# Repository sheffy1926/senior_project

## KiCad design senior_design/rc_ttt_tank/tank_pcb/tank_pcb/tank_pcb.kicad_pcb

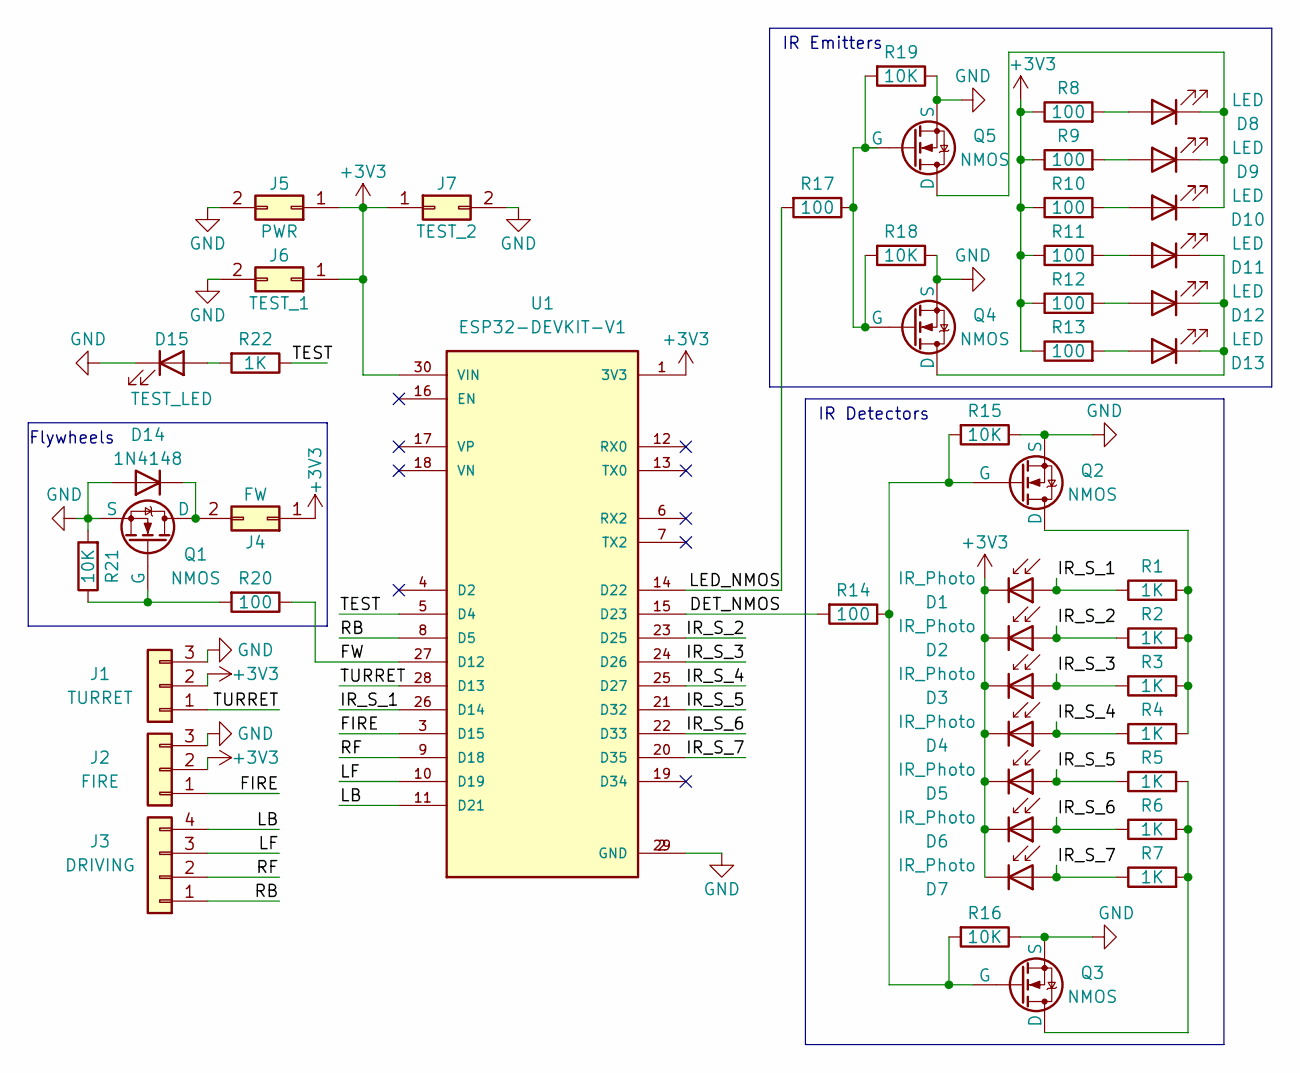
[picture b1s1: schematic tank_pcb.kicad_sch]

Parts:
D1, D2, D3, D4, D5, D6, D7: IR_Photo; LEDRD254W51D580H870
D8, D9, D10, D11, D12, D13: LED; LEDRD254W51D580H870
D14: 1N4148; D_DO-35_SOD27_P7.62mm_Horizontal
D15: TEST_LED; LED_D3.0mm
J1: TURRET; PinHeader_1x03_P2.54mm_Vertical
J2: FIRE; PinHeader_1x03_P2.54mm_Vertical
J3: DRIVING; PinHeader_1x04_P2.54mm_Vertical
J4: FW; PinHeader_1x02_P2.54mm_Vertical
J5: PWR; PinHeader_1x02_P2.54mm_Vertical
J6: TEST_1; PinHeader_1x02_P2.54mm_Vertical
J7: TEST_2; PinHeader_1x02_P2.54mm_Vertical
Q1, Q2, Q3, Q4, Q5: NMOS; SOT95P240X111-3N
R1, R2, R3, R4, R5, R6, R7, R22: 1K; R_Axial_DIN0204_L3.6mm_D1.6mm_P7.62mm_Horizontal
R8, R9, R10, R11, R12, R13, R14, R17, R20: 100; R_Axial_DIN0204_L3.6mm_D1.6mm_P7.62mm_Horizontal
R15, R16, R18, R19, R21: 10K; R_Axial_DIN0204_L3.6mm_D1.6mm_P7.62mm_Horizontal
U1: ESP32-DEVKIT-V1; MODULE_ESP32_DEVKIT_V1; PARTREV N/A

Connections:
+3V3: D1.1 (K), D2.1 (K), D3.1 (K), D4.1 (K), D5.1 (K), D6.1 (K), D7.1 (K), J1.2, J2.2, J4.1, J5.1, J6.1, J7.1, R8.1, R9.1, R10.1, R11.1, R12.1, R13.1, U1.1 (3V3), U1.30 (VIN)
/DET_NMOS: R14.2, U1.15 (D23)
/FIRE: J2.1, U1.3 (D15)
/FW: R20.1, U1.27 (D12)
/IR_S_1: D1.2 (A), R1.1, U1.26 (D14)
/IR_S_2: D2.2 (A), R2.1, U1.23 (D25)
/IR_S_3: D3.2 (A), R3.1, U1.24 (D26)
/IR_S_4: D4.2 (A), R4.1, U1.25 (D27)
/IR_S_5: D5.2 (A), R5.1, U1.21 (D32)
/IR_S_6: D6.2 (A), R6.1, U1.22 (D33)
/IR_S_7: D7.2 (A), R7.1, U1.20 (D35)
/LB: J3.4, U1.11 (D21)
/LED_NMOS: R17.2, U1.14 (D22)
/LF: J3.3, U1.10 (D19)
/RB: J3.1, U1.8 (D5)
/RF: J3.2, U1.9 (D18)
/TEST: R22.1, U1.5 (D4)
/TURRET: J1.1, U1.28 (D13)
GND: D14.2 (A), D15.1 (K), J1.3, J2.3, J5.2, J6.2, J7.2, Q1.3 (S), Q2.3 (S), Q3.3 (S), Q4.3 (S), Q5.3 (S), R15.1, R16.1, R18.1, R19.1, R21.2, U1.2 (GND), U1.29 (GND)
unnamed: D8.2 (A), R8.2
unnamed: D9.2 (A), R9.2
unnamed: D10.2 (A), R10.2
unnamed: D8.1 (K), D9.1 (K), D10.1 (K), Q5.1 (D)
unnamed: D11.2 (A), R11.2
unnamed: D11.1 (K), D12.1 (K), D13.1 (K), Q4.1 (D)
unnamed: D12.2 (A), R12.2
unnamed: D13.2 (A), R13.2
unnamed: D14.1 (K), J4.2, Q1.1 (D)
unnamed: D15.2 (A), R22.2
unnamed: Q1.2 (G), R20.2, R21.1
unnamed: Q2.1 (D), R1.2, R2.2, R3.2, R4.2
unnamed: Q2.2 (G), Q3.2 (G), R14.1, R15.2, R16.2
unnamed: Q3.1 (D), R5.2, R6.2, R7.2
unnamed: Q4.2 (G), Q5.2 (G), R17.1, R18.2, R19.2

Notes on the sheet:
IR Detectors
Flywheels
IR Emitters

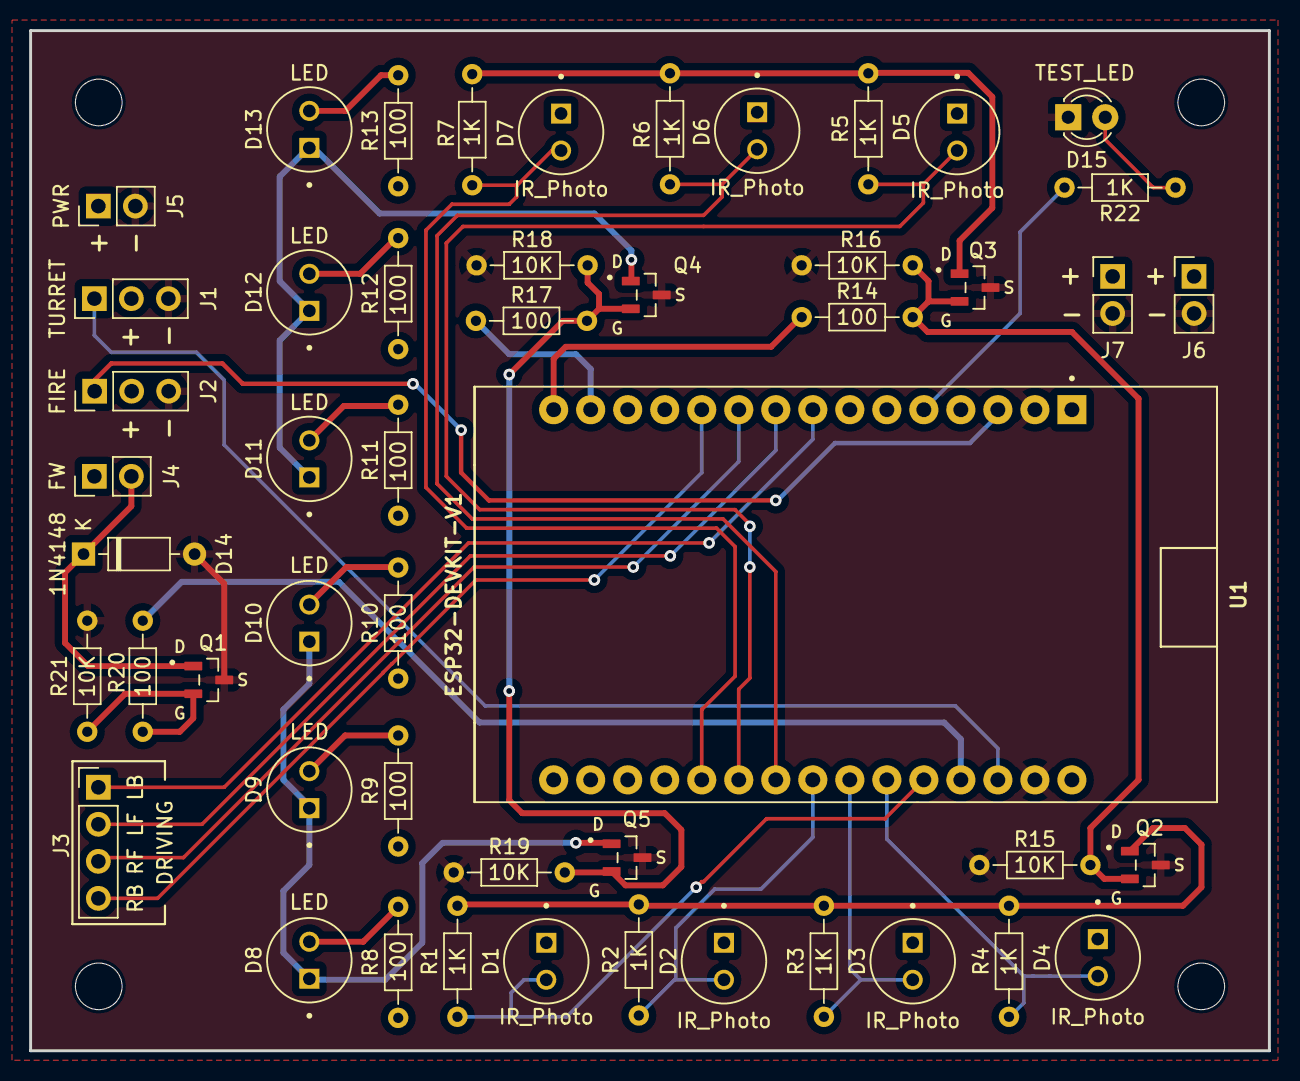
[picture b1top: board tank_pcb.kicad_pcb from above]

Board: 2 copper layers, 85.0 x 70.0 mm, 50 parts (0 on the bottom side), 34 nets.

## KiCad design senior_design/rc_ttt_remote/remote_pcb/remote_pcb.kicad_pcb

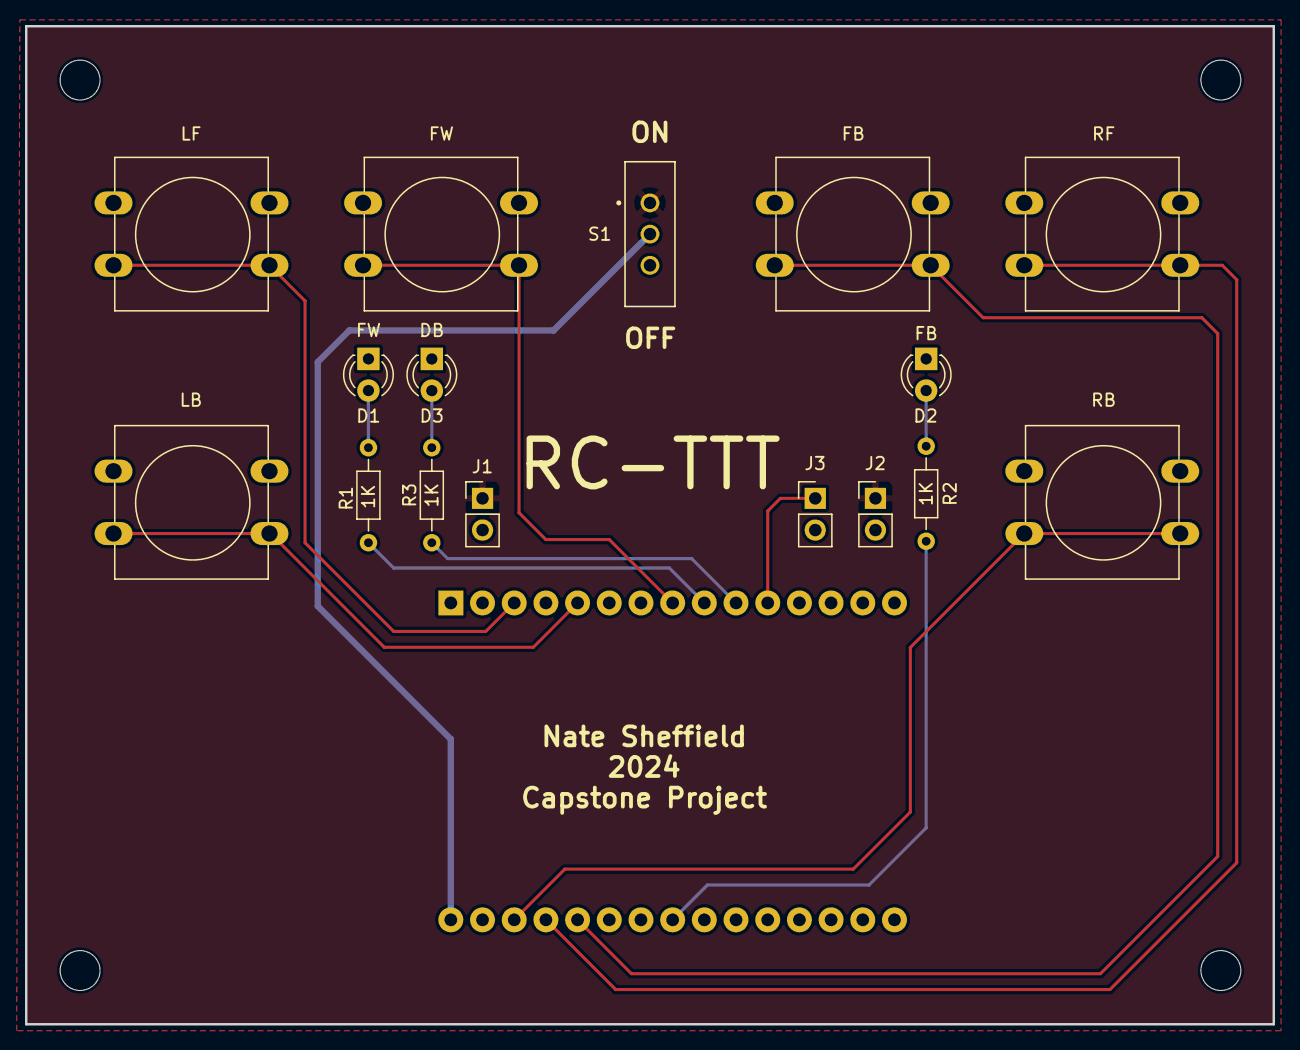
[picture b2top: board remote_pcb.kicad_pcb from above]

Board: 2 copper layers, 100.0 x 80.0 mm, 17 parts (1 on the bottom side), 16 nets.

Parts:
D1: FW; LED_D3.0mm
D2: FB; LED_D3.0mm
D3: DB; LED_D3.0mm
FB: FB; SW_PUSH-12mm
FW: FW; SW_PUSH-12mm
J1: PWR; PinHeader_1x02_P2.54mm_Vertical
J2: PWR_TEST; PinHeader_1x02_P2.54mm_Vertical
J3: PIN_TEST; PinHeader_1x02_P2.54mm_Vertical
LB: LB; SW_PUSH-12mm
LF: LF; SW_PUSH-12mm
R1, R2, R3: 1K; R_Axial_DIN0204_L3.6mm_D1.6mm_P7.62mm_Horizontal
RB: RB; SW_PUSH-12mm
RF: RF; SW_PUSH-12mm
S1: EG1218; SW_EG1218
U2: ESP32-DEVKIT-V1; MODULE_ESP32_DEVKIT_V1

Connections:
+3.3V: J1.1, J2.1, S1.1
GND: D1.1 (K), D2.1 (K), D3.1 (K), FB.1, FW.1, J1.2, J2.2, J3.2, LB.1, LF.1, RB.1, RF.1, U2.2 (GND), U2.29 (GND)
unnamed: D1.2 (A), R1.1
unnamed: D2.2 (A), R2.1
unnamed: D3.2 (A), R3.1
unnamed: J3.1, U2.11 (D21)
unnamed: LB.2, U2.5 (D4)
unnamed: FW.2, U2.8 (D5)
unnamed: RF.2, U2.27 (D12)
unnamed: RB.2, U2.28 (D13)
unnamed: FB.2, U2.26 (D14)
unnamed: LF.2, U2.3 (D15)
unnamed: R1.2, U2.9 (D18)
unnamed: R3.2, U2.10 (D19)
unnamed: R2.2, U2.23 (D25)
unnamed: S1.2, U2.30 (VIN)

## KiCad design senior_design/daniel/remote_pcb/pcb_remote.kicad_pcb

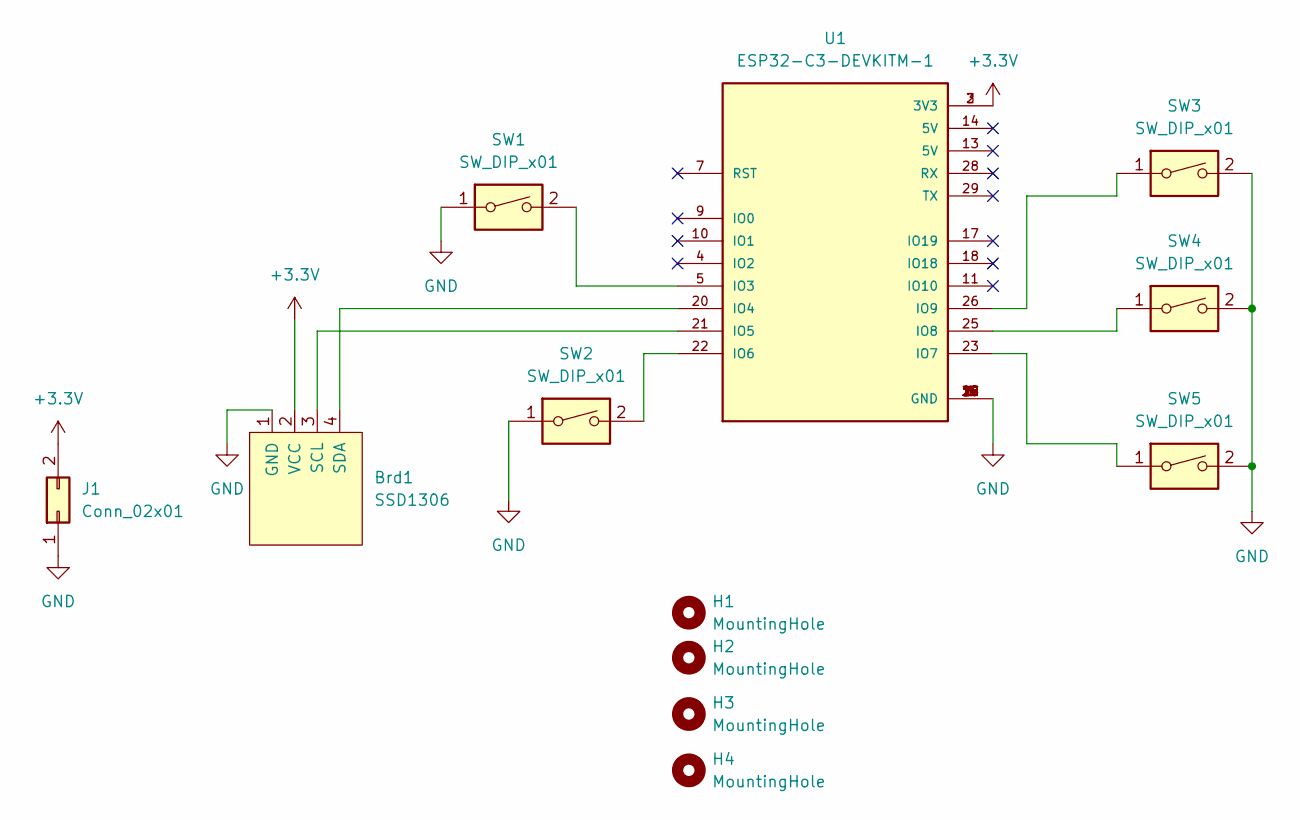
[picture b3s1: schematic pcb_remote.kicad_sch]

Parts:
Brd1: SSD1306; 128x64OLED
H1, H2, H3, H4: MountingHole; MountingHole_2.2mm_M2
J1: Conn_02x01; PinHeader_1x02_P2.54mm_Vertical
SW1, SW2, SW3, SW4, SW5: SW_DIP_x01; SW_PUSH-12mm
U1: ESP32-C3-DEVKITM-1; XCVR_ESP32-C3-DEVKITM-1

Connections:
+3V3: Brd1.2 (VCC), J1.2, U1.2 (3V3), U1.3 (3V3)
GND: Brd1.1 (GND), J1.1, SW1.1, SW2.1, SW3.2, SW4.2, SW5.2, U1.1 (GND), U1.6 (GND), U1.8 (GND), U1.12 (GND), U1.15 (GND), U1.16 (GND), U1.19 (GND), U1.24 (GND), U1.27 (GND), U1.30 (GND)
unnamed: Brd1.3 (SCL), U1.21 (IO5)
unnamed: Brd1.4 (SDA), U1.20 (IO4)
unnamed: SW1.2, U1.5 (IO3)
unnamed: SW2.2, U1.22 (IO6)
unnamed: SW3.1, U1.26 (IO9)
unnamed: SW4.1, U1.25 (IO8)
unnamed: SW5.1, U1.23 (IO7)

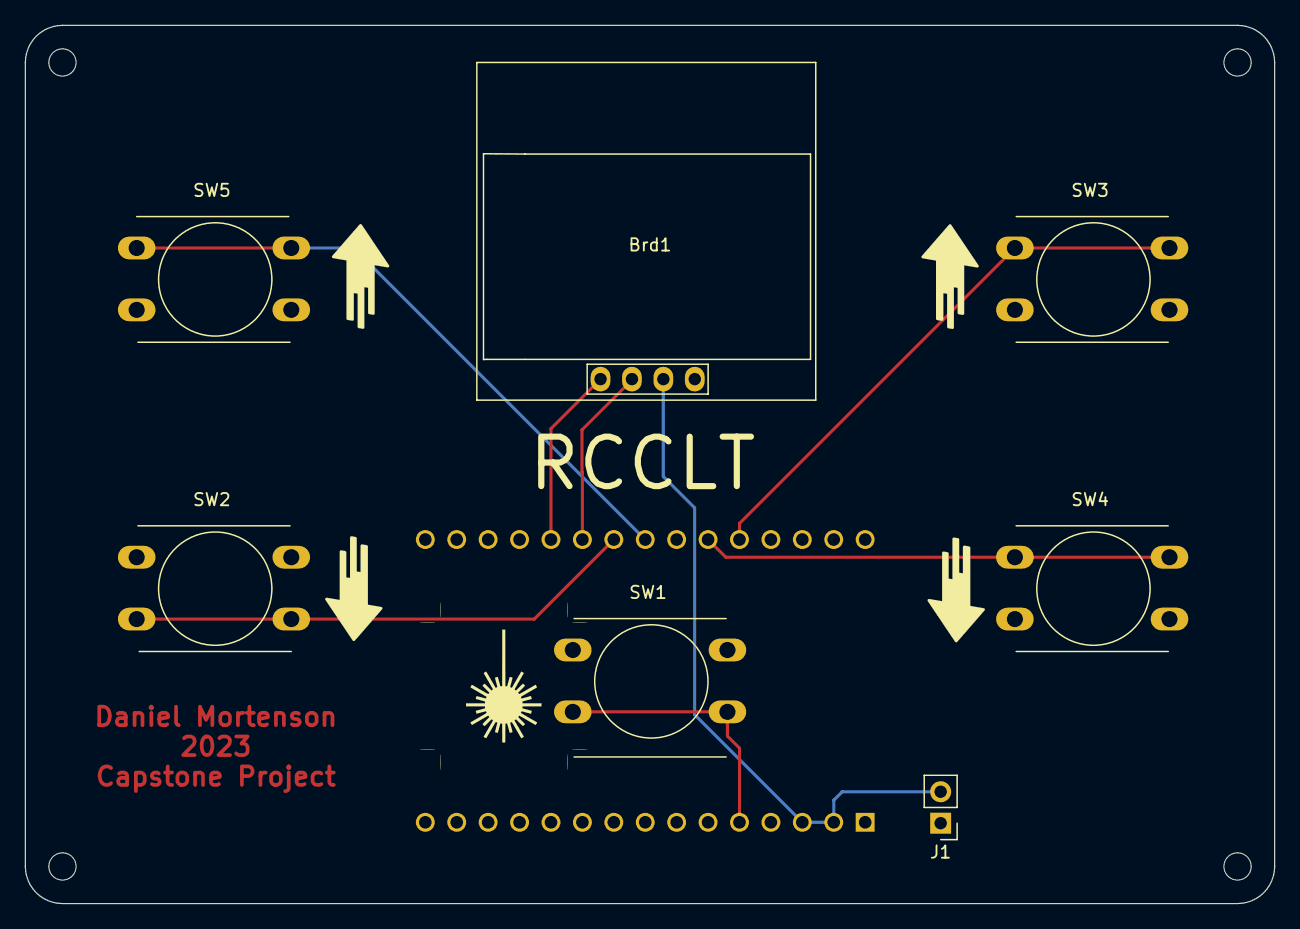
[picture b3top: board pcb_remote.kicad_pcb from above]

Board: 2 copper layers, 101.0 x 71.0 mm, 12 parts (1 on the bottom side), 9 nets.

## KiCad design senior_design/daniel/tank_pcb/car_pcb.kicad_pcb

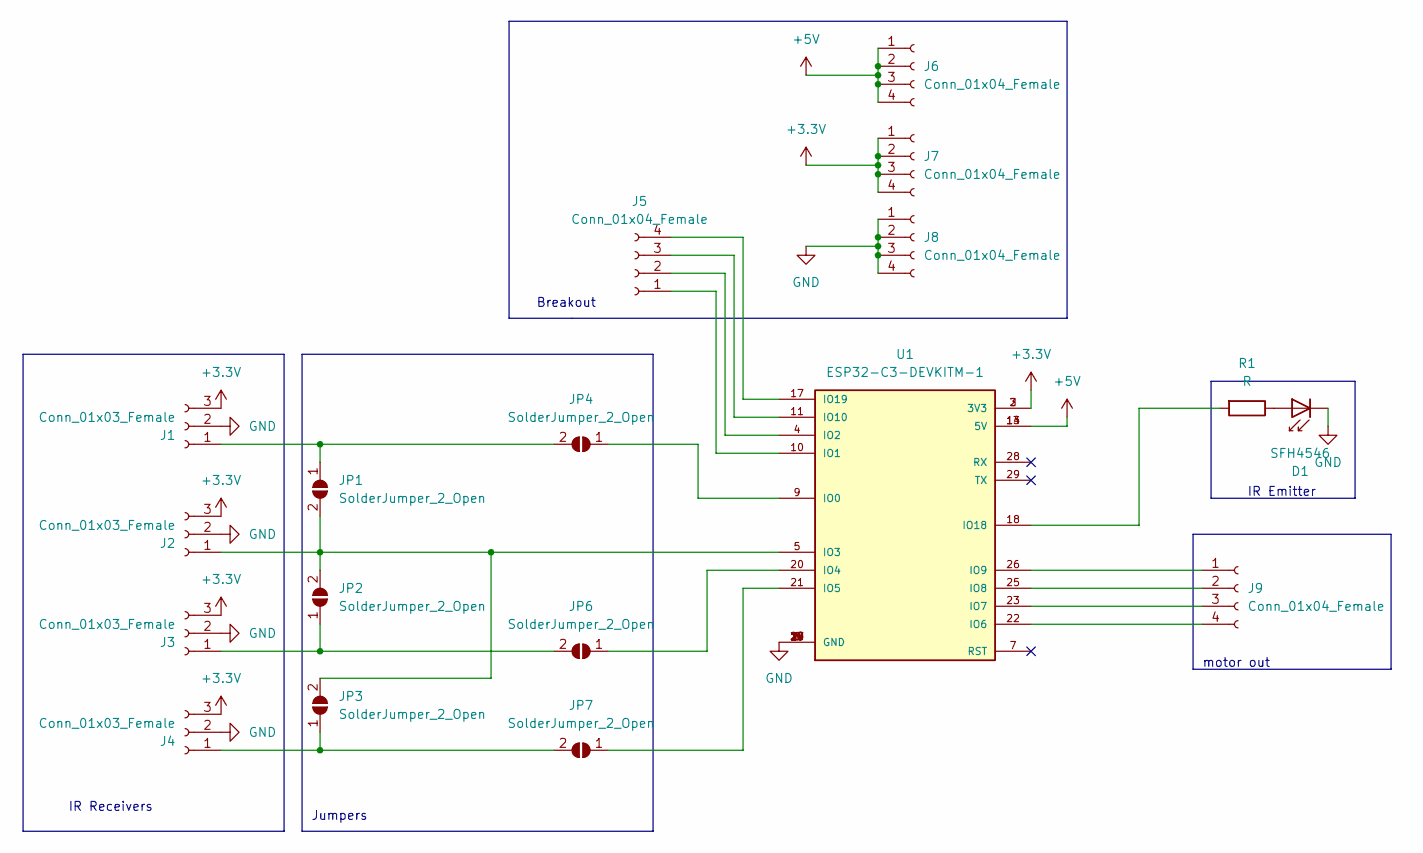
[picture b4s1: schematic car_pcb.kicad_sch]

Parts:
D1: SFH4546; LED_D5.0mm_IRGrey
J1, J2, J3, J4: Conn_01x03_Female; PinHeader_1x03_P2.54mm_Vertical
J5, J6, J7, J8, J9: Conn_01x04_Female; PinHeader_1x04_P2.54mm_Vertical
JP1, JP2, JP3: SolderJumper_2_Open; SolderJumper-2_P1.3mm_Open_TrianglePad1.0x1.5mm
JP4, JP6, JP7: SolderJumper_2_Open; SolderJumper-2_P1.3mm_Bridged_Pad1.0x1.5mm
R1: R; R_Axial_DIN0207_L6.3mm_D2.5mm_P10.16mm_Horizontal
U1: ESP32-C3-DEVKITM-1; XCVR_ESP32-C3-DEVKITM-1

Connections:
+3V3: J1.3, J2.3, J3.3, J4.3, J7.1, J7.2, J7.3, J7.4, U1.2 (3V3), U1.3 (3V3)
+5V: J6.1, J6.2, J6.3, J6.4, U1.13 (5V), U1.14 (5V)
GND: D1.1 (K), J1.2, J2.2, J3.2, J4.2, J8.1, J8.2, J8.3, J8.4, U1.1 (GND), U1.6 (GND), U1.8 (GND), U1.12 (GND), U1.15 (GND), U1.16 (GND), U1.19 (GND), U1.24 (GND), U1.27 (GND), U1.30 (GND)
unnamed: D1.2 (A), R1.1
unnamed: J1.1, JP1.1 (A), JP4.2 (B)
unnamed: J2.1, JP1.2 (B), JP2.2 (B), JP3.2 (B), U1.5 (IO3)
unnamed: J3.1, JP2.1 (A), JP6.2 (B)
unnamed: J4.1, JP3.1 (A), JP7.2 (B)
unnamed: J5.1, U1.10 (IO1)
unnamed: J5.2, U1.4 (IO2)
unnamed: J5.3, U1.11 (IO10)
unnamed: J5.4, U1.17 (IO19)
unnamed: J9.1, U1.26 (IO9)
unnamed: J9.2, U1.25 (IO8)
unnamed: J9.3, U1.23 (IO7)
unnamed: J9.4, U1.22 (IO6)
unnamed: JP4.1 (A), U1.9 (IO0)
unnamed: JP6.1 (A), U1.20 (IO4)
unnamed: JP7.1 (A), U1.21 (IO5)
unnamed: R1.2, U1.18 (IO18)

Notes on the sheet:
IR Receivers
IR Emitter
Breakout
motor out
Jumpers

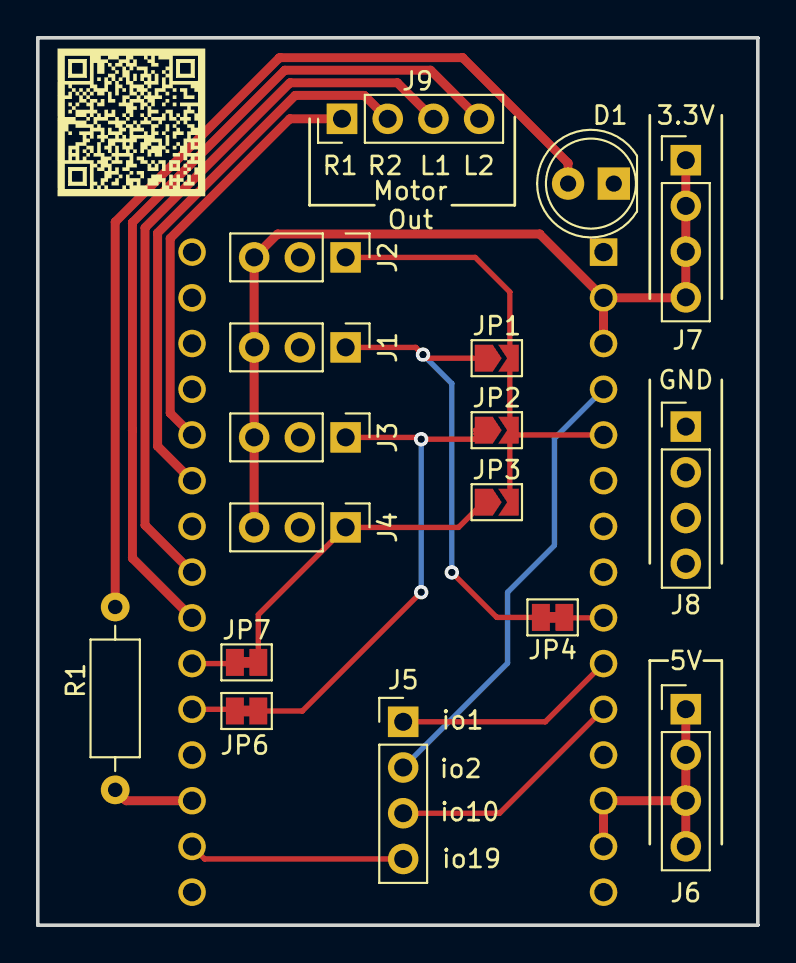
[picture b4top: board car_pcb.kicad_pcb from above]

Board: 2 copper layers, 40.0 x 49.3 mm, 18 parts (1 on the bottom side), 20 nets.

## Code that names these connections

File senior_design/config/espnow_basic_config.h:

#ifndef ESPNOW_BASIC_CONFIG_H
#define ESPNOW_BASIC_CONFIG_H

#include <inttypes.h>
#include <stdbool.h>

#define LINK	1
#define ZELDA	2
//change this value to compile for different tank remote pairs
#define TANK_REMOTE_PAIR ZELDA

#define ON 0
#define OFF 1
#define TRUE 1
#define FALSE 0
#define DEBOUNCE_DELAY_MS 30

//Tank Pins for Motors, Firing Mechanism, Flywheels, 
//PWM Signals, IR Sensors & Emitters
#define TEST_LED 4			//Test LED Pin If Needed
#define RB_IN1_PIN 5		//Right Back Pin
#define RF_IN2_PIN 18		//Right Forward Pin
#define LF_IN3_PIN 19		//Left Forward Pin
#define LB_IN4_PIN 21 		//Left Back Pin
#define TURRET_PIN 13		//Turret Servo Motor Pin
#define FIRE_PIN 15 		//Firing Mechanism Servo Motor Pin 
#define FW_NMOS 12			//Pin to activate Flywheels NMOS Low-Side Switch

#define IR_EMITS_NMOS 22 	//Pin to activate Emitters NMOS Low-Side Switch
#define IR_S_NMOS 23		//Pin to activate Detectors NMOS Low-Side Switch
//#define IR_S_1 14 		//				- ADC 2_6 (14)
//#define IR_S_2 36 		//-ADC 1_0 36	- ADC 2_8 (25)
//#define IR_S_3 39 		//-ADC 1_3 39 	- ADC 2_9 (26)
#define IR_S_4 34 			//-ADC 1_6 34   - ADC 2_7 (27)
#define IR_S_5 32 			//ADC 1_4 32
#define IR_S_6 33 			//ADC 1_5 33
#define IR_S_7 35 			//ADC 1_7 35 			

//Remote Pins for Buttons and LEDs
#define RF_BUT 12			//Right Forward Driving Button
#define RB_BUT 13			//Right Back Driving Button
#define LF_BUT 15			//Left Forward Driving Button
#define LB_BUT 4			//Left Back Driving Button
#define FIRE_BUT 14			//Activate Firing Mechanism Button
#define FW_BUT 5			//Toggle Flywheels Button
#define FIRE_LED 25			//Firing Status LED Pin
#define FW_LED 18			//Flywheel Status LED Pin

//Firing Servo Variables
#define SERVO_PWM_CHANNEL   	LEDC_CHANNEL_0
#define SERVO_PWM_TIMER     	LEDC_TIMER_0
#define DUTY_RESOLUTION 		8
#define PWM_FREQUENCY      		50 	// Hz
#define DUTY_MIN_FIRE       	8   // 8% duty cycle (0 degrees)
#define DUTY_MAX_FIRE       	24  // 20% duty cycle (90 degrees on this servo)
//Turret Servo Variables
#define TURRET_PWM_CHANNEL  	LEDC_CHANNEL_1
#define TURRET_PWM_TIMER    	LEDC_TIMER_1
#define DUTY_CYCLE_STEP			1
#define MIN_DUTY_CYCLE 			10
//19 for Zelda and 22 for Link
#define DUTY_CENTER				19	//(135 degrees - Centered) (MIN + MAX) / 2 
#define MAX_DUTY_CYCLE			32

#define ADC_WIDTH    	ADC_WIDTH_BIT_12
#define ADC_ATTEN    	ADC_ATTEN_DB_11 	// Attenuation level for ADC
#define V_REF    		1100        	 	// Default voltage reference (millivolts)
#define ADC_MAX_VALUE 	4095
#define MAX_VOLTAGE 	3.3
#define MIN_VOLTAGE		0.5

//message types
#define TANK_COMMAND  	1

// Define the structure of your data
typedef struct __attribute__((packed)) {
	//message type
	uint8_t message_type;

	//commands to the tank
    bool rf;
    bool rb;
    bool lf;
    bool lb;
	//commands to fire the turret
	bool fire_turret;
	bool activate_fw;
	bool fw_led;
} my_data_t;

//LINK
#define PAIR_1_TANK_MAC		{0xD8, 0x13, 0x2A, 0x7F, 0x9B, 0x34} 
#define PAIR_1_REMOTE_MAC	{0x48, 0xE7, 0x29, 0x96, 0x9C, 0xEC} 
#define PAIR_1_REMOTE_MAC_ARR	(uint8_t[])PAIR_1_REMOTE_MAC

//ZELDA
#define PAIR_2_TANK_MAC		{0xD8, 0x13, 0x2A, 0x7F, 0x9C, 0xFC}
#define PAIR_2_REMOTE_MAC	{0x10, 0x06, 0x1C, 0x41, 0xBD, 0x08}
#define PAIR_2_REMOTE_MAC_ARR	(uint8_t[])PAIR_2_REMOTE_MAC

#if TANK_REMOTE_PAIR == LINK
	#define TANK_MAC	PAIR_1_TANK_MAC	 
	#define REMOTE_MAC	PAIR_1_REMOTE_MAC
	//#define TANK_ID 1
	//#define REMOTE_ID 1

#elif TANK_REMOTE_PAIR == ZELDA
	#define TANK_MAC	PAIR_2_TANK_MAC	 
	#define REMOTE_MAC	PAIR_2_REMOTE_MAC
	//#define TANK_ID 2
	//#define REMOTE_ID 2
#endif

#define MY_ESPNOW_PMK "pmk1234567890123"
#define MY_ESPNOW_CHANNEL 1
// #define MY_ESPNOW_ENABLE_LONG_RANGE 1
#define MY_SLAVE_DEEP_SLEEP_TIME_MS 1000

#endif // ESPNOW_BASIC_CONFIG_H

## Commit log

2023-12-17 ESP NOW and Blink
2023-12-20 Removed Directories
2023-12-26 sound grenade v1
2024-01-12 Working LED strip code and updated old sound grenade code
2024-01-15 New Audio Files and Working Soldered Version
2024-01-25 Redid my file structure
2024-01-25 redid my file structure 2
2024-01-25 Modified from car to tank
2024-01-27 made tons of changes to espnow for tank and remote
2024-01-27 updated file structure and created esp-idf projects for tank and remote
2024-01-28 Added TODO list for remote and tank
2024-01-29 Cross checked espnow send and receive on both sides
2024-01-29 updated remote files still does not work properly
2024-01-29 Added Firing Mechanism Servo Task
2024-01-29 modified servo code
2024-01-30 modified the remote a bit
2024-02-02 updated firing buttons and button tasks.
2024-02-02 fixed firing button errors
2024-02-03 Remote Buttons Work!
2024-02-04 updated tank a little
2024-02-04 balance and updated espnow recv and send on tank and remote
2024-02-04 file structures synced however espnow still doesn't work
2024-02-05 minor update to sending struct
2024-02-05 minor updates to sending/recv struct
2024-02-05 Created schematic for remote pcb
2024-02-07 updated kicad files for remote
2024-02-09 updated github repository
2024-02-10 fixed tank mac address
2024-02-11 Sent and Received Data between remote and tank!
2024-02-11 updating sending and receiving
2024-02-11 got firing mechanism servo working
2024-02-11 corrected firing servo positions
2024-02-14 add queues, driving task and modified firing task
2024-02-14 add turret servo task
2024-02-15 Added Driving Init and created acceleration curves for driving pwm
2024-02-15 commented out queues and tried to fix motor controls. servos work okay but dc motors do not
2024-02-17 DC driving motors work without PWM signal
2024-02-17 added a turret button and tried to fix turret servo PWM
2024-02-19 Added Zelda's Remote and Tank MAC addresses
2024-02-19 fixed flashing with updated MAC addresses
2024-02-20 some adjustments
2024-02-20 improved firing button presses and tried fixing turret
2024-02-20 got turret to rotate consistently. Remote is fully functioning
2024-02-23 added tank_pcb folder and mosfet footprint files
2024-02-23 created tank_pcb schematic v1 and edited pins and pin names for tank
2024-02-26 finished design the tank pcb
2024-02-28 flashed tank code onto ZELDA tank esp32
2024-03-07 Added target tracking test code for IR s and e
2024-03-21 added transistors code, updated all of the pins for all components
2024-03-22 tried some new techniques to rotate the turret. they didn't work great
2024-03-26 I have the 11 rotation angle i will use for my turret.
2024-03-29 Redesigned my tank pcb. Also got ADC output on sensor 1 and was able to detect IR light!
2024-03-30 have 5 IR sensors working
2024-04-01 Sorting and rotating algorithm builds and flashes. Have not tested with turret yet.
2024-04-02 Fixed Stack overflow problem. Turret still is not rotating based on input angle
2024-04-02 sensors work but not transfering data to servo motors
2024-04-03 things are broken now and nothing runs and I really don't know why
2024-04-05 driving and firing works. algorithm is still too long needs to be broken up. Transistors don't work still
2024-04-18 The target tracking finally works with turret rotation! Only works with sensors 4-7 though
2024-04-22 minor cleanup of code
2024-05-01 got the turret recentered for Zelda. This is the final senior design night push for the RC-TTT
